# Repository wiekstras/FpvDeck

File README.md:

# FpvDeck

FpvDeck is an open handheld FPV field tool: a phone-sized 5-inch touchscreen,
dual 5.8 GHz analog receiver support, a low-latency FPV monitor, spectrum tools,
and a protected 2S–6S balance checker. It is a screen and field instrument—not
a radio transmitter.

> **CONCEPT RENDER — not mechanical CAD.** The enclosure and antenna placement
> remain subject to measured HAT, battery, connector, thermal, and RF clearances.

> **PARAMETRIC CONCEPT CAD.** The screen and mounting envelope use official
> Waveshare dimensions; connector positions and enclosure depth still require
> fit checks with received parts.

## Reference platform

- Waveshare ESP32-P4-WIFI6-Touch-LCD-5: ESP32-P4, ESP32-C6, 5-inch 720×1280
  MIPI-DSI IPS, GT911 capacitive touch, microSD, charger and 40-pin expansion.
- FpvDeck FPV HAT: two RX5808 receiver positions, hardware/MCU-selectable RSSI
  diversity, TVP5150AM1 video decoder, three ADS1115 ADCs, protected balance
  input, three buttons, buzzer and buffered analog AV output. Both SMA antenna
  connectors sit on the top edge, above their side-by-side RX5808 modules.
- Flat protected 1S LiPo, 3000–4000 mAh, connected only through the Waveshare
  board's documented battery connector.

The previous RadioMaster T8L/Linux-radio-computer direction was retired on
2026-10-26. It remains available in Git history through commit `fd47ebd`; no
T8L, ELRS or RC-transmitter function is part of the current product.

> **ENGINEERING LAYOUT CANDIDATE — NOT YET A FABRICATION RELEASE.** Both donor
> RX5808 locations, diversity/video electronics, decoder, ADCs and balance JST
> are placed. Donor-pad metrology, full routing, stack-up, DRC and bench safety
> gates remain open.

For an electrical/layout review, start with the focused
[FPV HAT peer-review guide](hardware/fpv-hat/REVIEW_GUIDE.md).

## Applications

| App | Purpose | State |
| --- | --- | --- |
| Battery | 2S–6S cells, total, delta, limits and storage hint | live ADS polling + host-tested math; HIL calibration pending |
| Monitor | Low-latency analog video, channel, dual RSSI and active receiver | live RSSI/active-RX overlay; video handoff needs HIL |
| Scanner | 48-channel A/B/E/F/R/L sweep, graph and strongest three channels | non-blocking live sweep; HIL RSSI calibration pending |
| Finder | Peak-hold RSSI, channel lock and proportional buzzer cadence | implemented; HIL cadence calibration pending |
| Stream | Local WPA2 SoftAP MJPEG spectator view | interface scaffold; encoder/network integration pending |
| Settings | Brightness, video standard, buzzer, calibration and Wi-Fi password | live persisted controls; calibration workflow pending |

## Field workflow

> **CONCEPT VISUALIZATION.** FpvDeck receives analog FPV independently while an
> external flight pack may be connected through its balance lead for measurement
> only. The pack's main discharge connector never powers FpvDeck.

## Build firmware

ESP-IDF **v6.1** is the pinned development release. Activate its environment,
then run:

```sh
idf.py set-target esp32p4
idf.py build
idf.py -p /dev/ttyACM0 flash monitor
```

The project defaults target ESP32-P4 rev3.x. Confirm the physical chip revision
before changing that profile.

## Run the simulator on macOS

The desktop simulator builds the same LVGL launcher and app screens used by the
ESP32-P4 firmware. It supplies deterministic virtual RX5808, video, balance
pack and Deck-battery backends, plus a fault-injection drawer.

```sh
brew install cmake sdl2 pkg-config
./scripts/simulator
```

Use the mouse as touch, the wheel to scroll, and arrow keys/Enter as the three
hardware buttons. The amber **SIM** control injects video loss/noise, balance
lead removal, 2S–6S packs, imbalance and low internal battery. Details and the
headless smoke test are in [simulator/README.md](simulator/README.md).

The source-controlled [UI captures](docs/assets/ui/) are generated from the
running LVGL simulator with `./scripts/simulator-screenshots`; they are not
static design mock-ups.

## Run host tests

Pure logic has no ESP-IDF dependency:

```sh
./scripts/test-host
```

This covers RX5808 channel/register math, battery tap subtraction and detection,
RSSI smoothing/peak hold, and scanner peak selection.

## Generate the HAT design

```sh
python3 hardware/gen_hat.py
```

The generator validates references, net connectivity, labels and balanced KiCad
syntax, then writes the KiCad schematic, BOM and audit netlist. The net-aware
four-layer layout candidate places all modeled parts and its two short RF
launches; it is explicitly **not released for fabrication** until the gates in
[hardware/READINESS.md](hardware/READINESS.md) are closed. See the
[RX5808/diversity research](hardware/research/RX5808_FINAL_HAT.md).

## Mechanical CAD

The adjustable [prototype clamshell](hardware/mechanical/prototype-shell/README.md)
includes the official display/mounting envelope, three-button rail, two SMA
passages and a side-entry JST-XH balance port. OpenSCAD source, STL exports and
review renders are committed. The [KiCad placement board](hardware/fpv-hat/README.md)
coordinates those connector locations and includes SVG/STEP exports. Both are
fit-check artifacts—not fabrication releases.

## Bring-up order

1. Inspect the unpowered HAT; verify no rail shorts.
2. Power only the Waveshare board and confirm 5 V/3.3 V header rails.
3. Fit the HAT without RX modules; scan I²C and confirm expected addresses.
4. Verify TVP5150 ID `0x51/0x50`, clock and reset timing.
5. Fit RX A with a dummy load/antenna and validate tuning plus RSSI.
6. Validate raw DVP capture before enabling PPA rotation/scaling and UI overlay.
7. Fit and validate RX B/diversity; then validate AV output.
8. Test balance inputs from a precision source before connecting a real LiPo.

See [the complete bring-up procedure](docs/BRINGUP.md).

## Documentation

- [Architecture](docs/ARCHITECTURE.md)
- [Hardware design](docs/HARDWARE.md)
- [Firmware design](docs/FIRMWARE.md)
- [macOS/desktop simulator](simulator/README.md)
- [Video and latency](docs/VIDEO.md)
- [Battery measurement](docs/BATTERY.md)
- [UI design](docs/UI.md)
- [Bring-up](docs/BRINGUP.md)
- [Decisions and open questions](DECISIONS.md)
- [Roadmap](TODO.md)

## Project status

- ✅ architecture reset and verified expansion-header mapping
- ✅ host-testable core logic and test runner
- ✅ ESP-IDF 6.1 firmware compiles for ESP32-P4 without warnings in project code
- ✅ native macOS/Linux LVGL simulator with touch, keyboard and fault injection
- 🚧 live sensor/video-to-display integration requires the physical stack
- 📐 generated 102-part KiCad schematic and final-form PCB layout candidate
- ⚠️ RX5808 module footprint/pinout requires physical verification
- ⚠️ no fabrication release or real-battery approval yet

## License

MIT. See [LICENSE](LICENSE).

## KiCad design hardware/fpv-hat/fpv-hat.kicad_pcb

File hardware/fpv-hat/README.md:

# FPV HAT Rev A

Generated artifacts:

- `fpv-hat.kicad_sch` — KiCad-readable annotated engineering schematic sheet;
- `fpv-hat.kicad_pcb` — four-layer, net-aware final-form placement candidate
  with all modeled parts and provisional short RF launches;
- `bom.csv` — per-reference part and assembly status;
- `netlist.txt` — authoritative checked connectivity audit;
- `fpv-hat-component-map.svg` — review view.
- `export/` — top/bottom assembly views and a placement-only STEP model.

Regenerate with `python3 hardware/gen_hat.py`. Do not edit generated files.
KiCad maintainers can regenerate the layout template with
`python3 hardware/gen_pcb_mechanical.py`, then export review views with
`./hardware/export_hat.sh`; these require KiCad's Python module and CLI.
The 28 × 23 mm RX5808 V1 footprint is provisional until checked against the
salvaged modules. This revision is intentionally not suitable for fabrication;
see [`../READINESS.md`](../READINESS.md) and the
[RX5808/diversity research](../research/RX5808_FINAL_HAT.md).

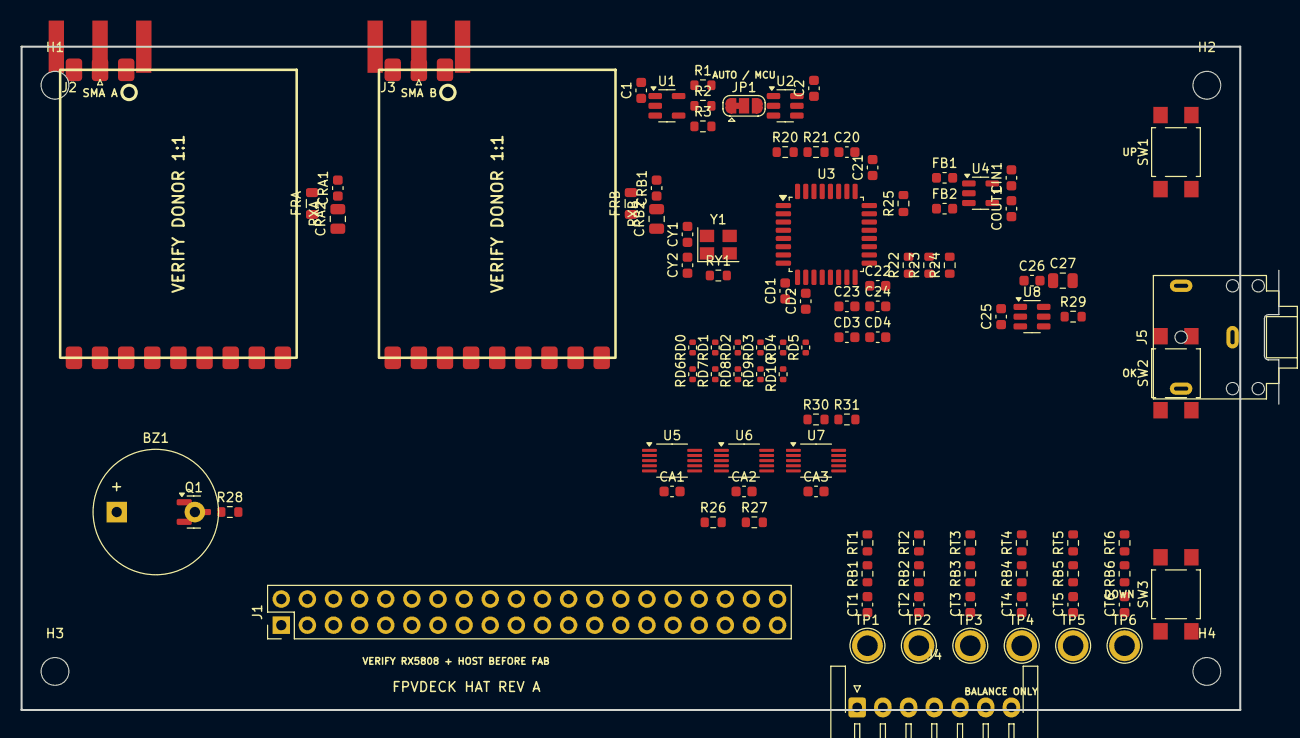
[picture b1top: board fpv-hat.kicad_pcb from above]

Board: 4 copper layers, 122.2 x 64.5 mm, 106 parts (0 on the bottom side), 82 nets.

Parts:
BZ1: MAGNETIC BUZZER; Buzzer_12x9.5RM7.6
C1, C2, C25, C26: 100n 16V X7R; C_0603_1608Metric
C20, C21: 100n; C_0603_1608Metric
C22, C23, C24: 1u; C_0603_1608Metric
C27: 4.7u 10V X7R; C_0805_2012Metric
CA1, CA2, CA3: 100n 16V X7R; C_0603_1608Metric
CD1, CD2, CD3, CD4: 100n 16V X7R; C_0603_1608Metric
CIN1: 1u 10V X7R; C_0603_1608Metric
COUT1: 1u 10V X7R; C_0603_1608Metric
CRA1: 100n 16V X7R; C_0603_1608Metric
CRA2: 10u 10V X7R; C_0805_2012Metric
CRB1: 100n 16V X7R; C_0603_1608Metric
CRB2: 10u 10V X7R; C_0805_2012Metric
CT1, CT2, CT3, CT4, CT5, CT6: 10n 50V C0G; C_0603_1608Metric
CY1, CY2: CRYSTAL LOAD TUNE; C_0603_1608Metric
FB1, FB2: 600R@100MHz; L_0603_1608Metric
FRA: 220R@100MHz 2A; L_0805_2012Metric
FRB: 220R@100MHz 2A; L_0805_2012Metric
H1, H2, H3, H4: M2.5; MountingHole_2.7mm_M2.5
J1: WAVESHARE 40PIN; PinHeader_2x20_P2.54mm_Vertical
J2: SMA EDGE A; SMA_Amphenol_132289_EdgeMount
J3: SMA EDGE B; SMA_Amphenol_132289_EdgeMount
J4: BALANCE 2S-6S; JST_XH_S7B-XH-A-1_1x07_P2.50mm_Horizontal
J5: AV OUT 3.5MM; Jack_3.5mm_CUI_SJ1-3523N_Horizontal
JP1: AUTO / MCU SELECT; SolderJumper-3_P1.3mm_Bridged12_RoundedPad1.0x1.5mm
Q1: BUZZER DRIVER; SOT-23
R1, R3: 10k 1%; R_0603_1608Metric
R2: 1M 1%; R_0603_1608Metric
R20, R21: 37.4R 1%; R_0603_1608Metric
R22, R23, R24, R25: 10k; R_0603_1608Metric
R26, R27: 100k; R_0603_1608Metric
R28: 2.2k; R_0603_1608Metric
R29: 75R 1%; R_0603_1608Metric
R30, R31: 1k; R_0603_1608Metric
RB1, RB2, RB3, RB4, RB5, RB6: 12k 1%; R_0603_1608Metric
RD0, RD1, RD2, RD3, RD4, RD5, RD6, RD7, RD8, RD9, RD10: 33R 1%; R_0402_1005Metric
RT1, RT2, RT3, RT4, RT5, RT6: 100k 1%; R_0603_1608Metric
RXA: RX5808 MODULE A; RX5808_V1_PROVISIONAL
RXB: RX5808 MODULE B; RX5808_V1_PROVISIONAL
RY1: 100k 1%; R_0603_1608Metric
SW1: UP; SW_SPST_TL3305A
SW2: OK; SW_SPST_TL3305A
SW3: DOWN; SW_SPST_TL3305A
TP1: TAP1; TestPoint_Plated_Hole_D2.0mm
TP2: TAP2; TestPoint_Plated_Hole_D2.0mm
TP3: TAP3; TestPoint_Plated_Hole_D2.0mm
TP4: TAP4; TestPoint_Plated_Hole_D2.0mm
TP5: TAP5; TestPoint_Plated_Hole_D2.0mm
TP6: TAP6; TestPoint_Plated_Hole_D2.0mm
U1: RSSI COMPARATOR; SOT-23-5
U2: VIDEO SWITCH; SOT-23-6
U3: CVBS DECODER; LQFP-32_7x7mm_P0.8mm
U4: 1.8V LDO; SOT-23-5
U5: ADS1115 0x48; VSSOP-10_3x3mm_P0.5mm
U6: ADS1115 0x49; VSSOP-10_3x3mm_P0.5mm
U7: ADS1115 0x4A; VSSOP-10_3x3mm_P0.5mm
U8: AV BUFFER; SOT-23-6
Y1: 14.31818MHz; Crystal_SMD_3225-4Pin_3.2x2.5mm

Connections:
+1V8: COUT1.1, FB1.1, FB2.1, U4.5
+1V8A: CD1.1, CD2.1, FB1.2, U3.4, U3.32
+1V8D: CD3.1, FB2.2, U3.20
+3V3: C1.1, C2.1, CA1.1, CA2.1, CA3.1, CD4.1, J1.2, J1.18, R1.2, U1.5, U2.5, U3.10, U3.28, U5.8, U6.1, U6.8, U7.8
+5V: BZ1.1, C26.1, C27.1, CIN1.1, FRA.1, FRB.1, J1.1, J1.3, U4.1, U4.3, U8.6
+5V_RX_A: CRA1.1, CRA2.1, FRA.2, RXA.8
+5V_RX_B: CRB1.1, CRB2.1, FRB.2, RXB.8
AGND: U3.3, U3.7, U3.31
AVID_PD: R23.1, U3.26
AV_BUF_IN: C25.2, U8.4
AV_BUF_OUT: R29.1, U8.2
BTN_DOWN: J1.38, SW3.1
BTN_OK: J1.37, SW2.1
BTN_UP: J1.36, SW1.1
BUZZER: J1.39, R28.1
BUZZER_BASE: Q1.1, R28.2
BUZZER_LOW: BZ1.2, Q1.3
DECK_ADC: R26.2, R27.1, U6.6
DVP_D0: J1.7, RD0.2
DVP_D0_RAW: RD0.1, U3.18
DVP_D1: J1.9, RD1.2
DVP_D1_RAW: RD1.1, U3.17
DVP_D2: J1.11, RD2.2
DVP_D2_RAW: RD2.1, U3.16
DVP_D3: J1.12, RD3.2
DVP_D3_RAW: RD3.1, U3.15
DVP_D4: J1.14, RD4.2
DVP_D4_RAW: RD4.1, U3.14
DVP_D5: J1.15, RD5.2
DVP_D5_RAW: RD5.1, U3.13
DVP_D6: J1.16, RD6.2
DVP_D6_RAW: RD6.1, U3.12
DVP_D7: J1.17, RD7.2
DVP_D7_RAW: R25.1, RD7.1, U3.11
DVP_HSYNC: J1.22, RD9.2
DVP_HSYNC_RAW: RD9.1, U3.25
DVP_PCLK: J1.20, RD8.2
DVP_PCLK_RAW: RD8.1, U3.9
DVP_VSYNC: J1.24, RD10.2
DVP_VSYNC_RAW: RD10.1, U3.24
FID_PD: R22.1, U3.23
GND: C1.2, C2.2, C21.2, C22.2, C23.2, C26.2, C27.2, CA1.2, CA2.2, CA3.2, CD1.2, CD2.2, CD3.2, CD4.2, CIN1.2, COUT1.2, CRA1.2, CRA2.2, CRB1.2, CRB2.2, CT1.2, CT2.2, CT3.2, CT4.2, CT5.2, CT6.2, CY1.2, CY2.2, J1.5, J1.26, J1.40, J2.2, J3.2, J4.1, Q1.2, R21.2, R22.2, R23.2, R24.2, R25.2, R27.2, RB1.2, RB2.2, RB3.2, RB4.2, RB5.2, RB6.2, RXA.1, RXA.3, RXA.7, RXA.12, RXB.1, RXB.3, RXB.7, RXB.12, SW1.2, SW2.2, SW3.2, U1.2, U2.2, U3.19, U4.2, U5.1, U5.3, U6.3, U7.3, U8.5, Y1.2, Y1.4
I2C_SCL: J1.6, U3.21, U5.10, U6.10, U7.10
I2C_SDA: J1.4, U3.22, U5.9, U6.9, U7.1, U7.9
INTREQ_PD: R24.1, U3.27
REFM: C23.1, C24.2, U3.30
REFP: C22.1, C24.1, U3.29
RF_A: J2.1, RXA.2
RF_B: J3.1, RXB.2
RSSI_A: R3.1, R30.1, RXA.9
RSSI_A_ADC: R30.2, U7.4
RSSI_A_HYS: R2.2, R3.2, U1.1
RSSI_B: R31.1, RXB.9, U1.3
RSSI_B_ADC: R31.2, U7.5
RX_A_STRONGER: JP1.1, R1.1, R2.1, U1.4
RX_CLK: J1.30, RXA.6, RXB.6
RX_DATA: J1.28, RXA.4, RXB.4
RX_LE_A: J1.31, RXA.5
RX_LE_B: J1.32, RXB.5
TAP1: J4.2, RT1.1, TP1.1
TAP1_ADC: CT1.1, RB1.1, RT1.2, U5.4
TAP2: J4.3, RT2.1, TP2.1
TAP2_ADC: CT2.1, RB2.1, RT2.2, U5.5
TAP3: J4.4, RT3.1, TP3.1
TAP3_ADC: CT3.1, RB3.1, RT3.2, U5.6
TAP4: J4.5, RT4.1, TP4.1
TAP4_ADC: CT4.1, RB4.1, RT4.2, U5.7
TAP5: J4.6, RT5.1, TP5.1
TAP5_ADC: CT5.1, RB5.1, RT5.2, U6.4
TAP6: J4.7, RT6.1, TP6.1
TAP6_ADC: CT6.1, RB6.1, RT6.2, U6.5
TVP_AIP1A: C20.2, U3.1
TVP_AIP1B: C21.1, U3.2
TVP_RESETB: J1.35, U3.8
VIDEO_A: RXA.11, U2.1
VIDEO_B: RXB.11, U2.3
VIDEO_SELECT: J1.34, JP1.2, U2.6
VIDEO_SELECTED: C25.1, R20.1, U2.4
VIDEO_SELECT_MCU: J1.8, JP1.3
VIDEO_TERM: C20.1, R20.2, R21.1
XTAL1: CY1.1, RY1.1, U3.5, Y1.1
XTAL2: CY2.1, RY1.2, U3.6, Y1.3

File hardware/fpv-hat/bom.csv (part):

Reference,Value,Manufacturer part number,Footprint,Status,Assembly note
BZ1,MAGNETIC BUZZER,TMB12A05,Buzzer_Beeper:Buzzer_12x9.5RM7.6,REVIEW,Footprint and current require final chosen buzzer verification.
C1,100n 16V X7R,GRM188R71C104KA01D,Capacitor_SMD:C_0603_1608Metric,REQUIRED,Place directly at U1 comparator supply.
C2,100n 16V X7R,GRM188R71C104KA01D,Capacitor_SMD:C_0603_1608Metric,REQUIRED,Place directly at U2 video-switch supply.
C20,100n,GRM188R71H104KA93D,Capacitor_SMD:C_0603_1608Metric,REQUIRED,
C21,100n,GRM188R71H104KA93D,Capacitor_SMD:C_0603_1608Metric,REQUIRED,
C22,1u,GRM188R61A105KA61D,Capacitor_SMD:C_0603_1608Metric,REQUIRED,
C23,1u,GRM188R61A105KA61D,Capacitor_SMD:C_0603_1608Metric,REQUIRED,
C24,1u,GRM188R61A105KA61D,Capacitor_SMD:C_0603_1608Metric,REQUIRED,
C25,100n 16V X7R,GRM188R71C104KA01D,Capacitor_SMD:C_0603_1608Metric,REQUIRED,TPF131 sync-clamp input coupling.
C26,100n 16V X7R,GRM188R71C104KA01D,Capacitor_SMD:C_0603_1608Metric,REQUIRED,Place directly at TPF131 pin 6.
C27,4.7u 10V X7R,GRM21BR71A475KA73L,Capacitor_SMD:C_0805_2012Metric,REQUIRED,TPF131 local bulk bypass; parallel with C26.
CA1,100n 16V X7R,GRM188R71C104KA01D,Capacitor_SMD:C_0603_1608Metric,REQUIRED,Place directly at U5 VDD pin 8; TI-required bypass.
CA2,100n 16V X7R,GRM188R71C104KA01D,Capacitor_SMD:C_0603_1608Metric,REQUIRED,Place directly at U6 VDD pin 8; TI-required bypass.
CA3,100n 16V X7R,GRM188R71C104KA01D,Capacitor_SMD:C_0603_1608Metric,REQUIRED,Place directly at U7 VDD pin 8; TI-required bypass.
CD1,100n 16V X7R,GRM188R71C104KA01D,Capacitor_SMD:C_0603_1608Metric,REQUIRED,TVP5150 PLL_AVDD pin 4 bypass; place at pin.
CD2,100n 16V X7R,GRM188R71C104KA01D,Capacitor_SMD:C_0603_1608Metric,REQUIRED,TVP5150 CH_AVDD pin 32 bypass; place at pin.
CD3,100n 16V X7R,GRM188R71C104KA01D,Capacitor_SMD:C_0603_1608Metric,REQUIRED,TVP5150 DVDD pin 20 bypass; place at pin.
CD4,100n 16V X7R,GRM188R71C104KA01D,Capacitor_SMD:C_0603_1608Metric,REQUIRED,TVP5150 IO_DVDD pin 10 bypass; place at pin.
CIN1,1u 10V X7R,GRM188R61A105KA61D,Capacitor_SMD:C_0603_1608Metric,REQUIRED,ME6211 input bypass; place at U4 pin 1.
COUT1,1u 10V X7R,GRM188R61A105KA61D,Capacitor_SMD:C_0603_1608Metric,REQUIRED,ME6211 output stability capacitor; place at U4 pin 5.
CRA1,100n 16V X7R,GRM188R71C104KA01D,Capacitor_SMD:C_0603_1608Metric,REQUIRED,Place at RXA power pad.
CRA2,10u 10V X7R,GRM21BR71A106KE51L,Capacitor_SMD:C_0805_2012Metric,REQUIRED,Receiver-A local bulk capacitor.
CRB1,100n 16V X7R,GRM188R71C104KA01D,Capacitor_SMD:C_0603_1608Metric,REQUIRED,Place at RXB power pad.
CRB2,10u 10V X7R,GRM21BR71A106KE51L,Capacitor_SMD:C_0805_2012Metric,REQUIRED,Receiver-B local bulk capacitor.
CT1,10n 50V C0G,GRM1885C1H103JA01D,Capacitor_SMD:C_0603_1608Metric,REQUIRED,
CT2,10n 50V C0G,GRM1885C1H103JA01D,Capacitor_SMD:C_0603_1608Metric,REQUIRED,
CT3,10n 50V C0G,GRM1885C1H103JA01D,Capacitor_SMD:C_0603_1608Metric,REQUIRED,
CT4,10n 50V C0G,GRM1885C1H103JA01D,Capacitor_SMD:C_0603_1608Metric,REQUIRED,
CT5,10n 50V C0G,GRM1885C1H103JA01D,Capacitor_SMD:C_0603_1608Metric,REQUIRED,
CT6,10n 50V C0G,GRM1885C1H103JA01D,Capacitor_SMD:C_0603_1608Metric,REQUIRED,
CY1,CRYSTAL LOAD TUNE,TBD_AFTER_OSCILLATOR_TEST,Capacitor_SMD:C_0603_1608Metric,DNP,Select from CL1=2*CL-Cstray; do not fit an unverified value.
CY2,CRYSTAL LOAD TUNE,TBD_AFTER_OSCILLATOR_TEST,Capacitor_SMD:C_0603_1608Metric,DNP,Match CY1 after measured board stray capacitance/oscillator test.
FB1,600R@100MHz,BLM18AG601SN1D,Inductor_SMD:L_0603_1608Metric,REQUIRED,
FB2,600R@100MHz,BLM18AG601SN1D,Inductor_SMD:L_0603_1608Metric,REQUIRED,
FRA,220R@100MHz 2A,BLM21PG221SN1D,Inductor_SMD:L_0805_2012Metric,REQUIRED,Dedicated receiver-A supply filter.
FRB,220R@100MHz 2A,BLM21PG221SN1D,Inductor_SMD:L_0805_2012Metric,REQUIRED,Dedicated receiver-B supply filter.
J1,WAVESHARE 40PIN,M20-9982046,Connector_PinHeader_2.54mm:PinHeader_2x20_P2.54mm_Vertical,REQUIRED,GPIO mapping is sourced from Waveshare schematic sheet 1/2.
J2,SMA EDGE A,132289-12,Connector_Coaxial:SMA_Amphenol_132289_EdgeMount,REQUIRED,
J3,SMA EDGE B,132289-12,Connector_Coaxial:SMA_Amphenol_132289_EdgeMount,REQUIRED,
J4,BALANCE 2S-6S,S7B-XH-A-1(LF)(SN),Connector_JST:JST_XH_S7B-XH-A-1_1x07_P2.50mm_Horizontal,REQUIRED,Side-entry external access; measurement only; no pack energy powers the Deck.
J5,AV OUT 3.5MM,SJ1-3523N,Connector_Audio:Jack_3.5mm_CUI_SJ1-3523N_Horizontal,REVIEW,
JP1,AUTO / MCU SELECT,SOLDER_JUMPER,Jumper:SolderJumper-3_P1.3mm_Bridged12_RoundedPad1.0x1.5mm,REQUIRED,Default 1-2 = hardware RSSI diversity; cut 1-2 and bridge 2-3 for MCU control.
Q1,BUZZER DRIVER,MMBT3904LT1G,Package_TO_SOT_SMD:SOT-23,REQUIRED,
R1,10k 1%,RC0603FR-0710KL,Resistor_SMD:R_0603_1608Metric,REQUIRED,Comparator open-drain pull-up.
R2,1M 1%,RC0603FR-071ML,Resistor_SMD:R_0603_1608Metric,REQUIRED,Comparator hysteresis feedback.
R20,37.4R 1%,RC0603FR-0737R4L,Resistor_SMD:R_0603_1608Metric,REQUIRED,
R21,37.4R 1%,RC0603FR-0737R4L,Resistor_SMD:R_0603_1608Metric,REQUIRED,
R22,10k,RC0603FR-0710KL,Resistor_SMD:R_0603_1608Metric,REQUIRED,
R23,10k,RC0603FR-0710KL,Resistor_SMD:R_0603_1608Metric,REQUIRED,
R24,10k,RC0603FR-0710KL,Resistor_SMD:R_0603_1608Metric,REQUIRED,
R25,10k,RC0603FR-0710KL,Resistor_SMD:R_0603_1608Metric,REQUIRED,I2CSEL low at reset.
R26,100k,RC0603FR-07100KL,Resistor_SMD:R_0603_1608Metric,DNP,Raw host BAT is not on the 40-pin header; do not fit or wire without review.
R27,100k,RC0603FR-07100KL,Resistor_SMD:R_0603_1608Metric,DNP,Reserved ADS channel; host GPIO20 already senses BAT through 200k/100k.
R28,2.2k,RC0603FR-072K2L,Resistor_SMD:R_0603_1608Metric,REQUIRED,
R29,75R 1%,RC0603FR-0775RL,Resistor_SMD:R_0603_1608Metric,REQUIRED,Source termination at U8 output.
R3,10k 1%,RC0603FR-0710KL,Resistor_SMD:R_0603_1608Metric,REQUIRED,
R30,1k,RC0603FR-071KL,Resistor_SMD:R_0603_1608Metric,REQUIRED,
R31,1k,RC0603FR-071KL,Resistor_SMD:R_0603_1608Metric,REQUIRED,
RB1,12k 1%,RC0603FR-0712KL,Resistor_SMD:R_0603_1608Metric,REQUIRED,
RB2,12k 1%,RC0603FR-0712KL,Resistor_SMD:R_0603_1608Metric,REQUIRED,
RB3,12k 1%,RC0603FR-0712KL,Resistor_SMD:R_0603_1608Metric,REQUIRED,
RB4,12k 1%,RC0603FR-0712KL,Resistor_SMD:R_0603_1608Metric,REQUIRED,
RB5,12k 1%,RC0603FR-0712KL,Resistor_SMD:R_0603_1608Metric,REQUIRED,
RB6,12k 1%,RC0603FR-0712KL,Resistor_SMD:R_0603_1608Metric,REQUIRED,
RD0,33R 1%,RC0402FR-0733RL,Resistor_SMD:R_0402_1005Metric,REQUIRED,
RD1,33R 1%,RC0402FR-0733RL,Resistor_SMD:R_0402_1005Metric,REQUIRED,
RD10,33R 1%,RC0402FR-0733RL,Resistor_SMD:R_0402_1005Metric,REQUIRED,
RD2,33R 1%,RC0402FR-0733RL,Resistor_SMD:R_0402_1005Metric,REQUIRED,
RD3,33R 1%,RC0402FR-0733RL,Resistor_SMD:R_0402_1005Metric,REQUIRED,
RD4,33R 1%,RC0402FR-0733RL,Resistor_SMD:R_0402_1005Metric,REQUIRED,
RD5,33R 1%,RC0402FR-0733RL,Resistor_SMD:R_0402_1005Metric,REQUIRED,
RD6,33R 1%,RC0402FR-0733RL,Resistor_SMD:R_0402_1005Metric,REQUIRED,
RD7,33R 1%,RC0402FR-0733RL,Resistor_SMD:R_0402_1005Metric,REQUIRED,
RD8,33R 1%,RC0402FR-0733RL,Resistor_SMD:R_0402_1005Metric,REQUIRED,
RD9,33R 1%,RC0402FR-0733RL,Resistor_SMD:R_0402_1005Metric,REQUIRED,
RT1,100k 1%,RC0603FR-07100KL,Resistor_SMD:R_0603_1608Metric,REQUIRED,
RT2,100k 1%,RC0603FR-07100KL,Resistor_SMD:R_0603_1608Metric,REQUIRED,
RT3,100k 1%,RC0603FR-07100KL,Resistor_SMD:R_0603_1608Metric,REQUIRED,
RT4,100k 1%,RC0603FR-07100KL,Resistor_SMD:R_0603_1608Metric,REQUIRED,
RT5,100k 1%,RC0603FR-07100KL,Resistor_SMD:R_0603_1608Metric,REQUIRED,
RT6,100k 1%,RC0603FR-07100KL,Resistor_SMD:R_0603_1608Metric,REQUIRED,
RXA,RX5808 MODULE A,RX5808 module,FPVDeck:RX5808_V1_PROVISIONAL,REQUIRED,SPEC V1 28x23x3 mm provisional land pattern; verify donor module pads 1:1.
RXB,RX5808 MODULE B,RX5808 module,FPVDeck:RX5808_V1_PROVISIONAL,REQUIRED,Second fitted receiver for final diversity assembly; verify donor module pads 1:1.
RY1,100k 1%,RC0603FR-07100KL,Resistor_SMD:R_0603_1608Metric,REQUIRED,TI SLES209E recommended parallel crystal resistor.
SW1,UP,TL3305AF160QG,Button_Switch_SMD:SW_SPST_TL3305A,REQUIRED,
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
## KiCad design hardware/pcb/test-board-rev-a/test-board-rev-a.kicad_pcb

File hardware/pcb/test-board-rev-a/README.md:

# FpvDeck Test PCB Rev A

This KiCad project is the modular bring-up board for the external balance checker,
real-time MCU, precision ADC, controls, low-speed module interfaces, and shutdown
coordination. It deliberately does **not** route MIPI DSI/CSI or integrate RF.

## Release state

**NOT RELEASED FOR FABRICATION.** The generated `.kicad_pcb` is a real KiCad board
with verified package classes, net intent, probe access, and mechanical placement.
It is not being represented as manufacturing-ready while these gates remain:

1. independently verify `ACASA1002U1002P1AT` pad-to-element pairing against the
   Vishay drawing and continuity-test a sample;
2. freeze and fault-test the protected B− reference path; provisional F2 must
   remain DNP until that review explicitly approves population;
3. complete the native schematic/ERC review;
4. route power, ground, analog and USB; add planes; run DRC;
5. peer-check the ADS8688A and STM32 pad maps against current datasheets;
6. validate every footprint against the exact ordered MPN, then print 1:1.

The component BOM and system order list intentionally place bare-PCB fabrication
in `WAIT` until these gates close. Compute, display, MCU development hardware and
measurement equipment can be ordered independently. The VRX and decoder remain
behind the documented end-to-end compatibility gate.

## Regeneration

KiCad 7 with its Python module is currently used:

```bash
python3 hardware/pcb/test-board-rev-a/generate_board.py
kicad-cli pcb export pdf -o /tmp/test-board.pdf \
  hardware/pcb/test-board-rev-a/test-board-rev-a.kicad_pcb
```

Generated output is source controlled so contributors can inspect the board
without running the generator. Do not hand-edit the generated PCB without also
updating or retiring the generator.

## Partitioning

- left: JST-XH input, precision divider arrays, raw/ADC test points;
- center: ADS8688A and STM32G0B1;
- bottom: current-limited bench 5 V and local 3.3 V;
- right: SBC header plus separate VRX-CVBS and decoder-CVBS breakouts;
- direct CM4-to-display DSI and decoder-to-CM4 CSI stay off-board.

F2 (`1206L010/60WR`) and TP33/TP34 provide a replaceable, probeable experiment
between `BNEG_RAW` and local ground; R7 explicitly connects `BNEG_RAW` to the
separate ADC `BNEG_SENSE` net. F2 is **not an approved protection design**.
The PPTC's normal resistance produces measurable offset, its trip behavior is not
a substitute for a complete ground-fault design, and USB/bench/SBC grounds can
create alternate current paths. Keep it DNP and use only a current-limited,
non-battery simulator until the release gate in `docs/BATTERY_MEASUREMENT.md`
closes.

The controlled experiment matrix is
[`docs/BALANCE_GROUND_FAULT_ANALYSIS.md`](../../../docs/BALANCE_GROUND_FAULT_ANALYSIS.md).

J4 and J5 deliberately connect only pin 2 ground and pin 3 CVBS. All other pins
are NC. The SteadyView X receiver is powered through its documented 6.5–26 V
barrel/XT60 ground-station harness, not Test PCB 5 V. The decoder EVM also keeps
its own documented power/control/MIPI connections. Rev A therefore proves the
analog handoff without inventing either module's internal pinout.

## Board documents and views

- [Layout](LAYOUT.md)
- [Component map](COMPONENT_MAP.md)
- [Build guide](BUILD_GUIDE.md)
- [Release readiness](READINESS.md)
- [Fabrication notes](FABRICATION_NOTES.md)

The committed [top](exports/test-board-rev-a-top.svg),
[bottom](exports/test-board-rev-a-bottom.svg), and
[component-map](exports/test-board-rev-a-component-map.svg) SVGs are inspection
views of the placed, unrouted board. They are not fabrication outputs.

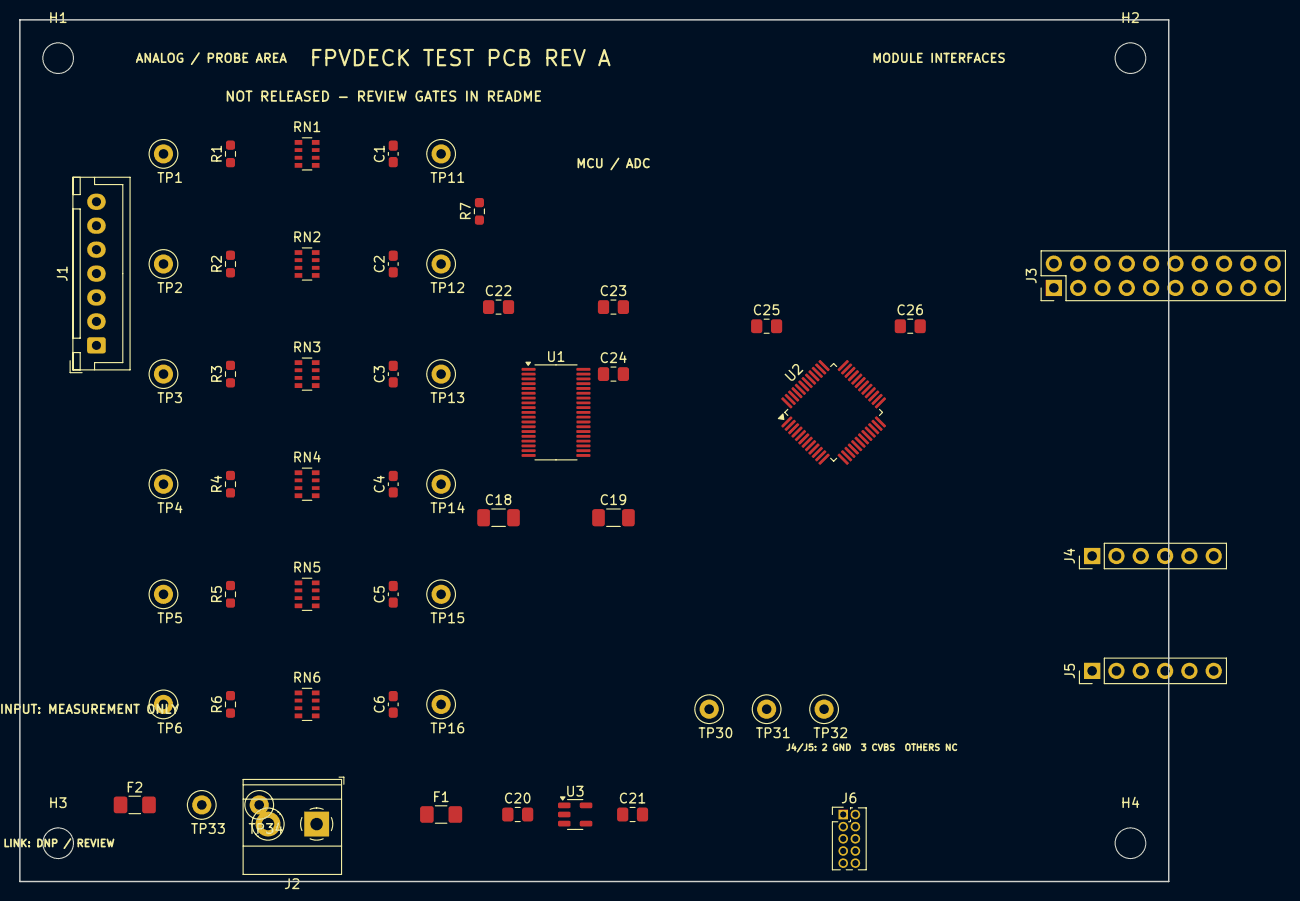
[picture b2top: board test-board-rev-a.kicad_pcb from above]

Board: 4 copper layers, 120.0 x 90.0 mm, 60 parts (0 on the bottom side), 52 nets, no tracks yet.

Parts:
C1, C2, C3, C4, C5, C6: 10n C0G 50V; C_0603_1608Metric_Pad1.08x0.95mm_HandSolder
C18, C19: 22u 10V X7R; C_1206_3216Metric_Pad1.33x1.80mm_HandSolder
C20, C21, C22, C23, C24: 1u 10V X7R; C_0805_2012Metric_Pad1.18x1.45mm_HandSolder
C25: 100n 16V X7R; C_0805_2012Metric_Pad1.18x1.45mm_HandSolder
C26: 4.7u 10V X7R; C_0805_2012Metric_Pad1.18x1.45mm_HandSolder
F1: MF-MSMF050-2; Fuse_1206_3216Metric_Pad1.42x1.75mm_HandSolder
F2: 1206L010/60WR DNP; Fuse_1206_3216Metric_Pad1.42x1.75mm_HandSolder
H1, H2, H3, H4: M3; MountingHole_3.2mm_M3
J1: B7B-XH-A(LF)(SN); JST_XH_B7B-XH-A_1x07_P2.50mm_Vertical
J2: 5V BENCH IN; TerminalBlock_Phoenix_MKDS-1,5-2-5.08_1x02_P5.08mm_Horizont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
J3: SBC LINK; PinHeader_2x10_P2.54mm_Vertical
J4: VRX CVBS ONLY; PinHeader_1x06_P2.54mm_Vertical
J5: DECODER CVBS ONLY; PinHeader_1x06_P2.54mm_Vertical
J6: SWD; PinHeader_2x05_P1.27mm_Vertical
R1, R2, R3, R4, R5, R6, R7: 1K00 0.1%; R_0603_1608Metric_Pad0.98x0.95mm_HandSolder
RN1, RN2, RN3, RN4, RN5, RN6: ACASA1002U1002P1AT; R_Array_Convex_4x0603
TP1: TAP1_RAW; TestPoint_Loop_D2.50mm_Drill1.0mm
TP2: TAP2_RAW; TestPoint_Loop_D2.50mm_Drill1.0mm
TP3: TAP3_RAW; TestPoint_Loop_D2.50mm_Drill1.0mm
TP4: TAP4_RAW; TestPoint_Loop_D2.50mm_Drill1.0mm
TP5: TAP5_RAW; TestPoint_Loop_D2.50mm_Drill1.0mm
TP6: TAP6_RAW; TestPoint_Loop_D2.50mm_Drill1.0mm
TP11: TAP1_ADC; TestPoint_Loop_D2.50mm_Drill1.0mm
TP12: TAP2_ADC; TestPoint_Loop_D2.50mm_Drill1.0mm
TP13: TAP3_ADC; TestPoint_Loop_D2.50mm_Drill1.0mm
TP14: TAP4_ADC; TestPoint_Loop_D2.50mm_Drill1.0mm
TP15: TAP5_ADC; TestPoint_Loop_D2.50mm_Drill1.0mm
TP16: TAP6_ADC; TestPoint_Loop_D2.50mm_Drill1.0mm
TP30: 5V; TestPoint_Loop_D2.50mm_Drill1.0mm
TP31: 3V3; TestPoint_Loop_D2.50mm_Drill1.0mm
TP32: GND; TestPoint_Loop_D2.50mm_Drill1.0mm
TP33: BNEG_RAW; TestPoint_Loop_D2.50mm_Drill1.0mm
TP34: LOCAL_GND; TestPoint_Loop_D2.50mm_Drill1.0mm
U1: ADS8688AIDBT; TSSOP-38_4.4x9.7mm_P0.5mm
U2: STM32G0B1CBT6; LQFP-48_7x7mm_P0.5mm
U3: TLV75533PDBVR; SOT-23-5

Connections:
+3V3: C21.1, C24.1, C25.1, C26.1, J3.3, J6.1, TP31.1, U1.34, U2.4, U2.5, U2.6, U3.5
+5V_FUSED: C20.1, C22.1, C23.1, F1.2, J3.1, TP30.1, U1.9, U1.30, U3.1, U3.3
+5V_RAW: F1.1, J2.1
ADC_ALARM: U1.35, U2.21
ADC_CS: U1.38, U2.19
ADC_REFCAP: C19.1, U1.7
ADC_REFIO: C18.1, U1.5
ADC_RESET: U1.2, U2.20
BNEG_RAW: F2.1, J1.1, R7.1, TP33.1
BNEG_SENSE: R7.2, U1.12
GND: C1.2, C2.2, C3.2, C4.2, C5.2, C6.2, C18.2, C19.2, C20.2, C21.2, C22.2, C23.2, C24.2, C25.2, C26.2, F2.2, J2.2, J3.2, J3.4, J4.2, J5.2, J6.3, J6.5, RN1.5, RN2.5, RN3.5, RN4.5, RN5.5, RN6.5, TP32.1, TP34.1, U1.3, U1.4, U1.6, U1.8, U1.11, U1.13, U1.15, U1.17, U1.19, U1.20, U1.22, U1.24, U1.26, U1.28, U1.29, U1.31, U1.32, U1.33, U2.7, U3.2
I2C_SCL: J3.9, U2.47
I2C_SDA: J3.10, U2.48
NRST: J6.10, U2.10
SPI_MISO: U1.36, U2.17
SPI_MOSI: U1.1, U2.18
SPI_SCLK: U1.37, U2.16
SWCLK: J6.4, U2.36
SWDIO: J6.2, U2.35
TAP1_ADC: C1.1, RN1.4, RN1.6, TP11.1, U1.16
TAP1_RAW: J1.2, R1.1, TP1.1
TAP1_SER: R1.2, RN1.1
TAP1_STAGE1: RN1.2, RN1.8
TAP1_STAGE2: RN1.3, RN1.7
TAP2_ADC: C2.1, RN2.4, RN2.6, TP12.1, U1.18
TAP2_RAW: J1.3, R2.1, TP2.1
TAP2_SER: R2.2, RN2.1
TAP2_STAGE1: RN2.2, RN2.8
TAP2_STAGE2: RN2.3, RN2.7
TAP3_ADC: C3.1, RN3.4, RN3.6, TP13.1, U1.21
TAP3_RAW: J1.4, R3.1, TP3.1
TAP3_SER: R3.2, RN3.1
TAP3_STAGE1: RN3.2, RN3.8
TAP3_STAGE2: RN3.3, RN3.7
TAP4_ADC: C4.1, RN4.4, RN4.6, TP14.1, U1.23
TAP4_RAW: J1.5, R4.1, TP4.1
TAP4_SER: R4.2, RN4.1
TAP4_STAGE1: RN4.2, RN4.8
TAP4_STAGE2: RN4.3, RN4.7
TAP5_ADC: C5.1, RN5.4, RN5.6, TP15.1, U1.25
TAP5_RAW: J1.6, R5.1, TP5.1
TAP5_SER: R5.2, RN5.1
TAP5_STAGE1: RN5.2, RN5.8
TAP5_STAGE2: RN5.3, RN5.7
TAP6_ADC: C6.1, RN6.4, RN6.6, TP16.1, U1.27
TAP6_RAW: J1.7, R6.1, TP6.1
TAP6_SER: R6.2, RN6.1
TAP6_STAGE1: RN6.2, RN6.8
TAP6_STAGE2: RN6.3, RN6.7
UART_RX: J3.6, U2.14
UART_TX: J3.5, U2.13
VRX_VIDEO: J4.3, J5.3

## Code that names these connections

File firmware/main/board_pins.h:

#pragma once

/*
 * Single source of truth for FpvDeck HAT pin assignments.
 * Source: Waveshare ESP32-P4-WIFI6-Touch-LCD-5 schematic, sheet 1/2,
 * connector J3; cross-checked against the official 40-pin table on 2026-10-26.
 * Pins 21/23 (USB-FS capable) and 25/27 (dedicated USB-HS) are not used.
 */

#define PIN_I2C_SDA       7   /* J3 pin 4,  schematic sheet 1/2: SDA/GPIO7 */
#define PIN_I2C_SCL       8   /* J3 pin 6,  schematic sheet 1/2: SCL/GPIO8 */

#define PIN_DVP_D0       37   /* J3 pin 7,  schematic sheet 1/2: GPIO37 */
#define PIN_VIDEO_SELECT_MCU 2 /* J3 pin 8, schematic sheet 1/2: GPIO2; JP1 option */
#define PIN_DVP_D1       38   /* J3 pin 9,  schematic sheet 1/2: GPIO38 */
#define PIN_DVP_D2        5   /* J3 pin 11, schematic sheet 1/2: GPIO5 */
#define PIN_DVP_D3        3   /* J3 pin 12, schematic sheet 1/2: GPIO3 */
#define PIN_DVP_D4        4   /* J3 pin 14, schematic sheet 1/2: GPIO4 */
#define PIN_DVP_D5       21   /* J3 pin 15, schematic sheet 1/2: GPIO21 */
#define PIN_DVP_D6       28   /* J3 pin 16, schematic sheet 1/2: GPIO28 */
#define PIN_DVP_D7       22   /* J3 pin 17, schematic sheet 1/2: GPIO22 */
#define PIN_DVP_PCLK     29   /* J3 pin 20, schematic sheet 1/2: GPIO29 */
#define PIN_DVP_HSYNC    30   /* J3 pin 22, schematic sheet 1/2: GPIO30 */
#define PIN_DVP_VSYNC    31   /* J3 pin 24, schematic sheet 1/2: GPIO31 */

#define PIN_RX_DATA      34   /* J3 pin 28, schematic sheet 1/2: GPIO34 */
#define PIN_RX_CLK       35   /* J3 pin 30, schematic sheet 1/2: GPIO35 */
#define PIN_RX_LE_A      32   /* J3 pin 31, schematic sheet 1/2: GPIO32 */
#define PIN_RX_LE_B      49   /* J3 pin 32, schematic sheet 1/2: GPIO49 */
#define PIN_ACTIVE_RX    50   /* J3 pin 34, sheet 1/2: VIDEO_SELECT; high = RX A */
#define PIN_TVP_RESETB   46   /* J3 pin 35, schematic sheet 1/2: GPIO46 */
#define PIN_BUTTON_UP    51   /* J3 pin 36, schematic sheet 1/2: GPIO51 */
#define PIN_BUTTON_OK    47   /* J3 pin 37, schematic sheet 1/2: GPIO47 */
#define PIN_BUTTON_DOWN  52   /* J3 pin 38, schematic sheet 1/2: GPIO52 */
#define PIN_BUZZER       48   /* J3 pin 39, schematic sheet 1/2: GPIO48 */

/* Host-board net, not a 40-pin HAT signal: sheet 1/2 BAT_ADC -> GPIO20. */
#define PIN_DECK_BATTERY_ADC 20

#define HAT_HEADER_5V_PIN_A   1
#define HAT_HEADER_5V_PIN_B   3
#define HAT_HEADER_3V3_PIN_A  2
#define HAT_HEADER_3V3_PIN_B 18
